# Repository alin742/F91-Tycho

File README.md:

# F91 Tycho

F91 Tycho is a continuation of **[F91 Kepler](https://github.com/drpykachu/F91_Kepler)** by Pegor (originally on [GitLab](https://gitlab.com/_Pegor/kepler_fw)), a full replacement of the Casio F-91W internals with an OLED display and a Bluetooth CC2640R2 MCU. All credit for the original design goes to them; this repo keeps their full history and MIT license.

What's new here:
- **Rechargeable v2:** LIR2016 cell, BQ25180 charger, TPS62840 buck, and a small charging PCB in the case back's dip with a magnetic pogo cable ([main board](Hardware/KiCad/F91-Main_board_v2/README.md), [charging PCB](Hardware/KiCad/F91-Charge_pad/README.md), [JLC panel](Hardware/KiCad/panel/README.md)).
- **KiCad import** of the original DipTrace boards (`Hardware/KiCad/`).
- **Firmware:** battery-life work, v2 charger/battery support (written, not yet compiled).
- **SolidCraft** case + electronics model (`Hardware/SolidCraft/`).
- Open work: [TASKS.md](TASKS.md).

Code identifiers (`f91_kepler.c`, project names, file names) keep the Kepler name so the original build setup still works.

---

## Original F91 Kepler README

## 8/8/25 - This project hasn't been active for a while, but I have kept it around for anyone interested in it or wants to draw inspiration from it. I have moved it from its [original repo](https://gitlab.com/_Pegor/kepler_fw) since I use GitHub more these days. 

The F91 Kepler is complete redesign of the classic Casio F91W watch. This project completely replaces the original internals of the watch only keeping the original case and adding an OLED display and a bluetooth capable MCU.

This repo contains all the firmware, hardware, and completely unfinished software (phone app) ;).

## As of 7/18/22 the current state of the project is:
- Bluetooth capable and supports several calls.
- Only operates through bluetooth diagnostic apps such as nRF Connect.
- Full screen notifications for calls/texts.
- Notifications bar.
- Only one button currently supported to wake screen.
- Battery life of roughly 15 days with waking screen several times a day.

## To-do / improvements:
- Create phone app to handle sending BLE calls automatically.
- Add ability to set time through buttons.
- Add sound capabilities (PCB already contains traces). 
- Improve battery life and efficiency.
- Improve programming jig (make it easier to use without having to completely dismantle).
- Make rechargeable

### At this point (read more like a year ago) I am burnt out from this project and now I figured to open it up and hopefully more people can be involved.

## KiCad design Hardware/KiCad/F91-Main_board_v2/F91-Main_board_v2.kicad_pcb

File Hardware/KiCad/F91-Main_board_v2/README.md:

# F91 Tycho v2 main board (rechargeable)

LIR2016 rechargeable coin cell → **BQ25180** charger → **TPS62840** buck → **2.0 V** for the CC2640R2,
OLED logic and I2C. The board keeps the v1 outline, holder holes, castellated button contacts,
PCB antenna and the v1 RF matching network. Every assembled part is in the JLCPCB library.

Status: **design files generated, not yet built or tested.** See "Check before ordering" below.

## Files
| File | What |
|---|---|
| `F91-Main_board_v2.kicad_sch` | Schematic (net labels, generated) |
| `F91-Main_board_v2.kicad_pcb` | Board: 24.4 × 24.4 mm, 2 layers, 0.8 mm |
| `F91-Main_board_v2.kicad_pro/.kicad_dru` | JLCPCB 2-layer rules (0.1/0.1 mm tracks, vias 0.45/0.25 and 0.6/0.3, both standard price) + castellation / RF / antenna rules |
| `lib/F91_LCSC.*` | Symbols, footprints, 3D models pulled from LCSC with easyeda2kicad (the footprints JLC places to) |
| `lib/F91_custom.pretty` | Antenna, battery pads, castellations, holes, charge-pin holes (from v1 geometry) |
| `scripts/` | The generators (see "Regenerating") |
| `../F91-Charge_pad/` | Obsolete charging PCB (replaced by the two charge pins) |
| `../panel/` | JLC panel (2 × 2 main boards), fab export |

## Circuit summary
- **Cell:** LIR2016 under the original clamp. Clamp = battery +, the cell's flat side = GND pads (as v1).
- **Charger BQ25180** (U2, DSBGA-8, I2C 0x6A): power-up defaults are safe for the LIR2016 with no firmware (4.20 V, 10 mA, BUVLO 3.0 V). /INT → DIO6 (pin 11). TS/MR left open (TS off, no NTC).
- **Buck TPS62840** (U3, DSBGA-6): EN = SYS, VSET = 1.74 kΩ → 2.0 V, 60 nA Iq. L1 2.2 µH.
- **CC2640R2** in internal-LDO mode: the v1 10 µH DC/DC inductor is removed, DCDC_SW is unconnected. Firmware must disable the DC/DC in ccfg (done in `Startup/ccfg_app_ble.c` for `F91_HW_V2`).
- **Battery sense:** 10 MΩ / 1 MΩ divider + 100 nF into DIO23 (ADC). About 0.38 µA.
- **Buttons:** the clamp arm (battery +) touches the castellation, which drives an N-FET gate (PMZB290UNE, 1 MΩ pull-down); the FET pulls DIO15/25/26 low → buttons are **active-low with internal pull-ups** (firmware `F91_HW_V2`).
- **Display connector J1** (Molex 505066, same position as v1). Top row: GND, SCL, **VBAT (new, for the SSD1306 charge pump VDDB)**. Bottom row: **VDD 2.0 V (was battery)**, SDA, NC.
- **Charging input:** two plated Ø1.3 mm holes (Ø1.7 pads) P1 (+, CHG_IN) and P2 (GND) at board (12.80, −3.40) / (11.19, −5.32), watch (9.75, 6.17) / (8.14, 8.09), 2.5 mm apart. Hand-solder a Ø1.2 mm brass pin in each, sticking 1.85 mm out of the bottom (flush with the inner face of the steel back); they meet the pogo cable through two Ø1.8 mm holes in the steel back. D1 (PMEG3002AEL reverse-polarity Schottky), D2 (TPD1E10B06 ESD) and R24 (1 M pull-down) sit next to them.
- **Programming:** cJTAG pads at the v1 jig positions: GND, VDD (sense only), TMS, TCK (the v1 jig fits). The v1 UART and RESET pads were dropped for space; the XDS110 resets the chip over cJTAG. Power the board from the battery pads or from 5 V on the charge pins, never by back-feeding VDD.
- **No external flash:** firmware updates over Bluetooth must use TI **on-chip OAD**. There was no room for an SPI flash: the bottom corners are cut by the board chamfer or taken by the charge pins.

## Display adapter rework (reuse the v1 adapter, no new board)
The v1 adapter ties SSD1306 VDD (logic, max 3.3 V) and VDDB (charge pump, 3.3–4.2 V) to one connector pin. On v2 that pin carries 2.0 V, so the charge pump needs its own supply:
1. Cut the trace between the SSD1306 **VDDB** pin and VDD/VCC on the adapter.
2. Solder a thin enamelled wire from **VDDB** to the adapter connector pin that mates with J1's **top-right** pin (the free pin next to SCL, carrying VBAT on v2).
3. Optional: remove the adapter's duplicate 10 kΩ I2C pull-ups (the main board has 10 kΩ to VDD).

## Status of the generated board
- **DRC: 0 errors, 0 unconnected pads** (`kicad-cli pcb drc --schematic-parity`). 11 warnings: 10 courtyard overlaps (mostly inherited from v1's placement: castellation vs button pad, MH2 vs C8, TP pads near U1) and one 0.087 mm neck where a track enters Q2's pad.
- **Schematic parity:** all nets match. The only differences reported are KiCad's placeholder names for no-connect pins.
- **ERC:** 0 violations.
- Routing was done by `scripts/router2.py` (own grid router; Freerouting was not available here). Look it over in KiCad before ordering, especially around U1 pins 1–10, the charger (U2) and buck (U3) pockets, and the RF chain (copied unchanged from v1).
- Every via is tented. The cell's negative face sits on Pad3/Pad4 + the U1 thermal-via area (all GND).

## Check before ordering
- JLC stock on order day: CC2640R2FRGZR (600 when checked), BQ25180YBGR, TPS62840YBGR.
- In JLC's placement preview, check the rotation of U1 (QFN), U2/U3 (DSBGA), Q1–Q3 (DFN1006) and J1 (Molex).
- Case-open measurements (TASKS.md): clamp outline, piezo position, case-back thickness, clamp-to-case-back contact. Check the mode-button clamp arm stays clear of the charge pins.

## Regenerating
```
cd Hardware/KiCad/F91-Main_board_v2
python3 scripts/gen_footprints.py     # custom footprints from the v1 board
python3 scripts/gen_project.py        # .kicad_pro rules + .kicad_dru
python3 scripts/gen_sch.py            # schematic from scripts/design.py
python3 scripts/gen_pcb.py            # board: v1 geometry + placement (placement/place.json) + fixed escapes
python3 scripts/fanout_gnd.py         # short track + via for every small GND pad
python3 scripts/router2.py 40         # negotiated-congestion router (all nets but GND)
python3 scripts/nudge_vias.py F91-Main_board_v2.kicad_pcb work/drc.rpt   # after a DRC, fixes ~0.01 mm misses
python3 scripts/pour.py               # GND pours + stitching vias
python3 scripts/link_gnd_clusters.py  # joins any GND piece the pour left isolated
python3 scripts/finalize.py F91-Main_board_v2.kicad_pcb   # hide refdes, board label
../../../tools/kikit-venv/bin/python ../panel/panelize.py
python3 ../panel/export_fab.py        # gerbers zip + JLC BOM/CPL
```
`scripts/design.py` is the single source of truth for parts, values, LCSC numbers and nets.

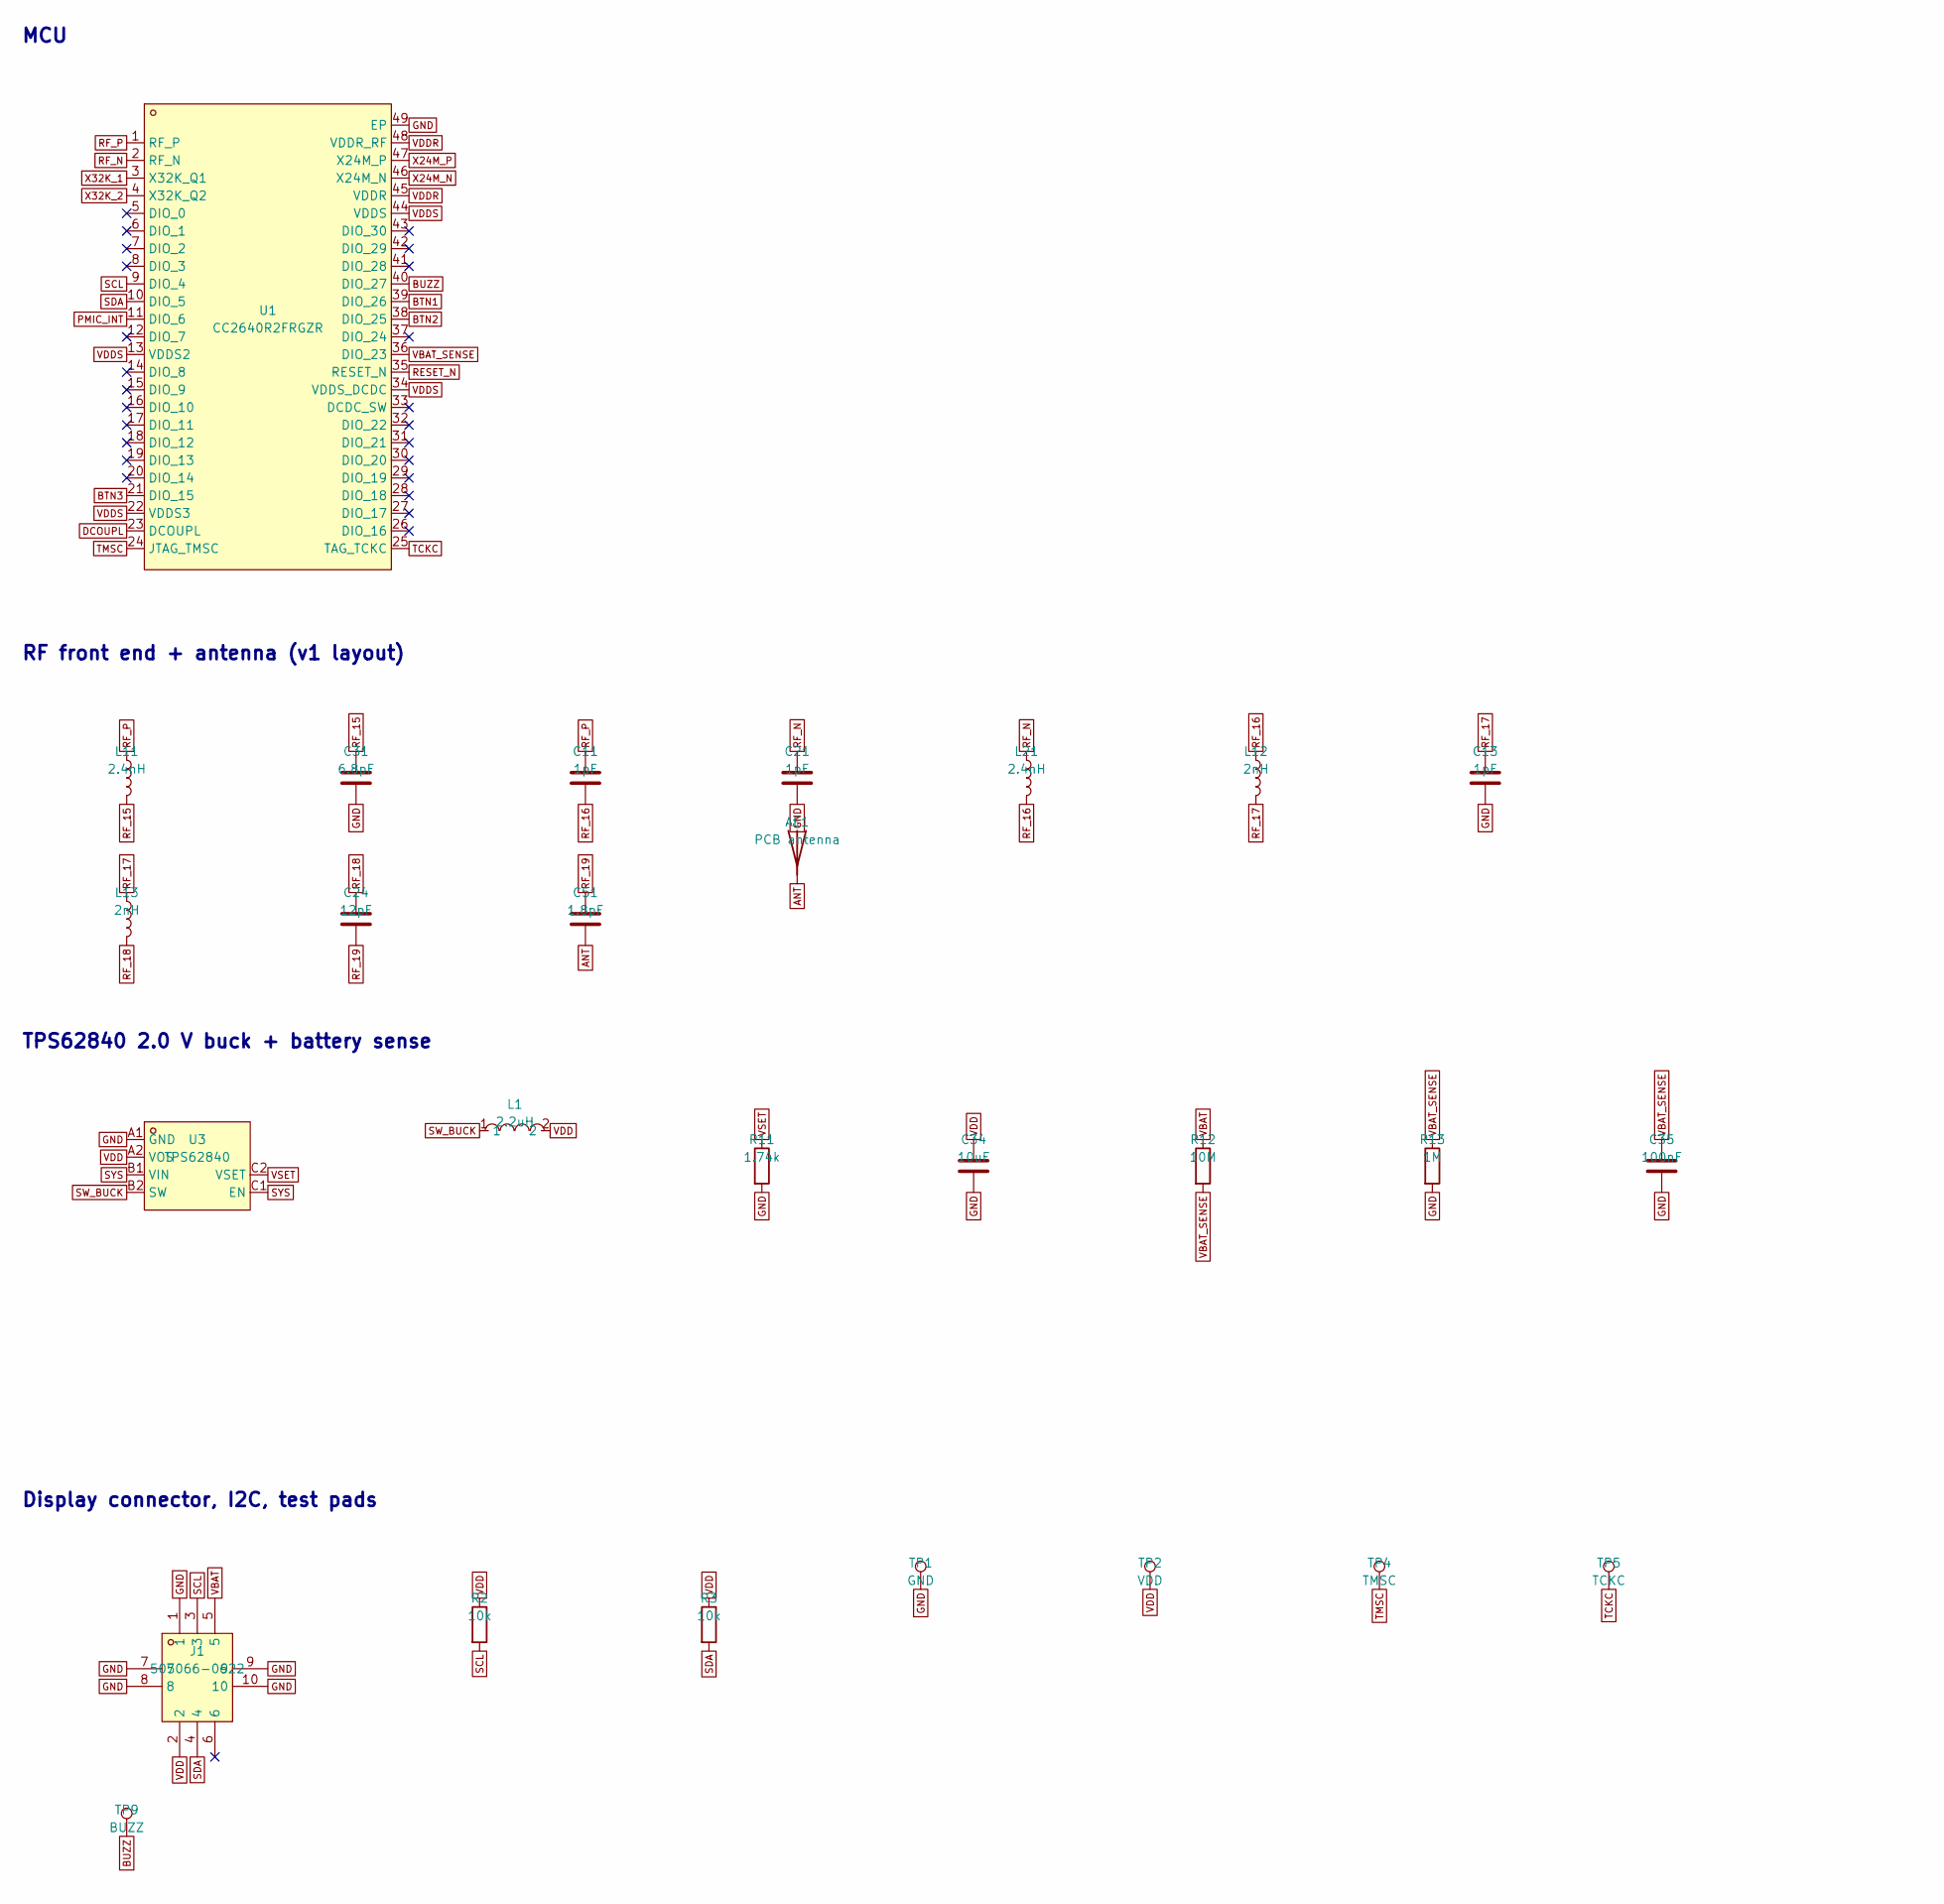
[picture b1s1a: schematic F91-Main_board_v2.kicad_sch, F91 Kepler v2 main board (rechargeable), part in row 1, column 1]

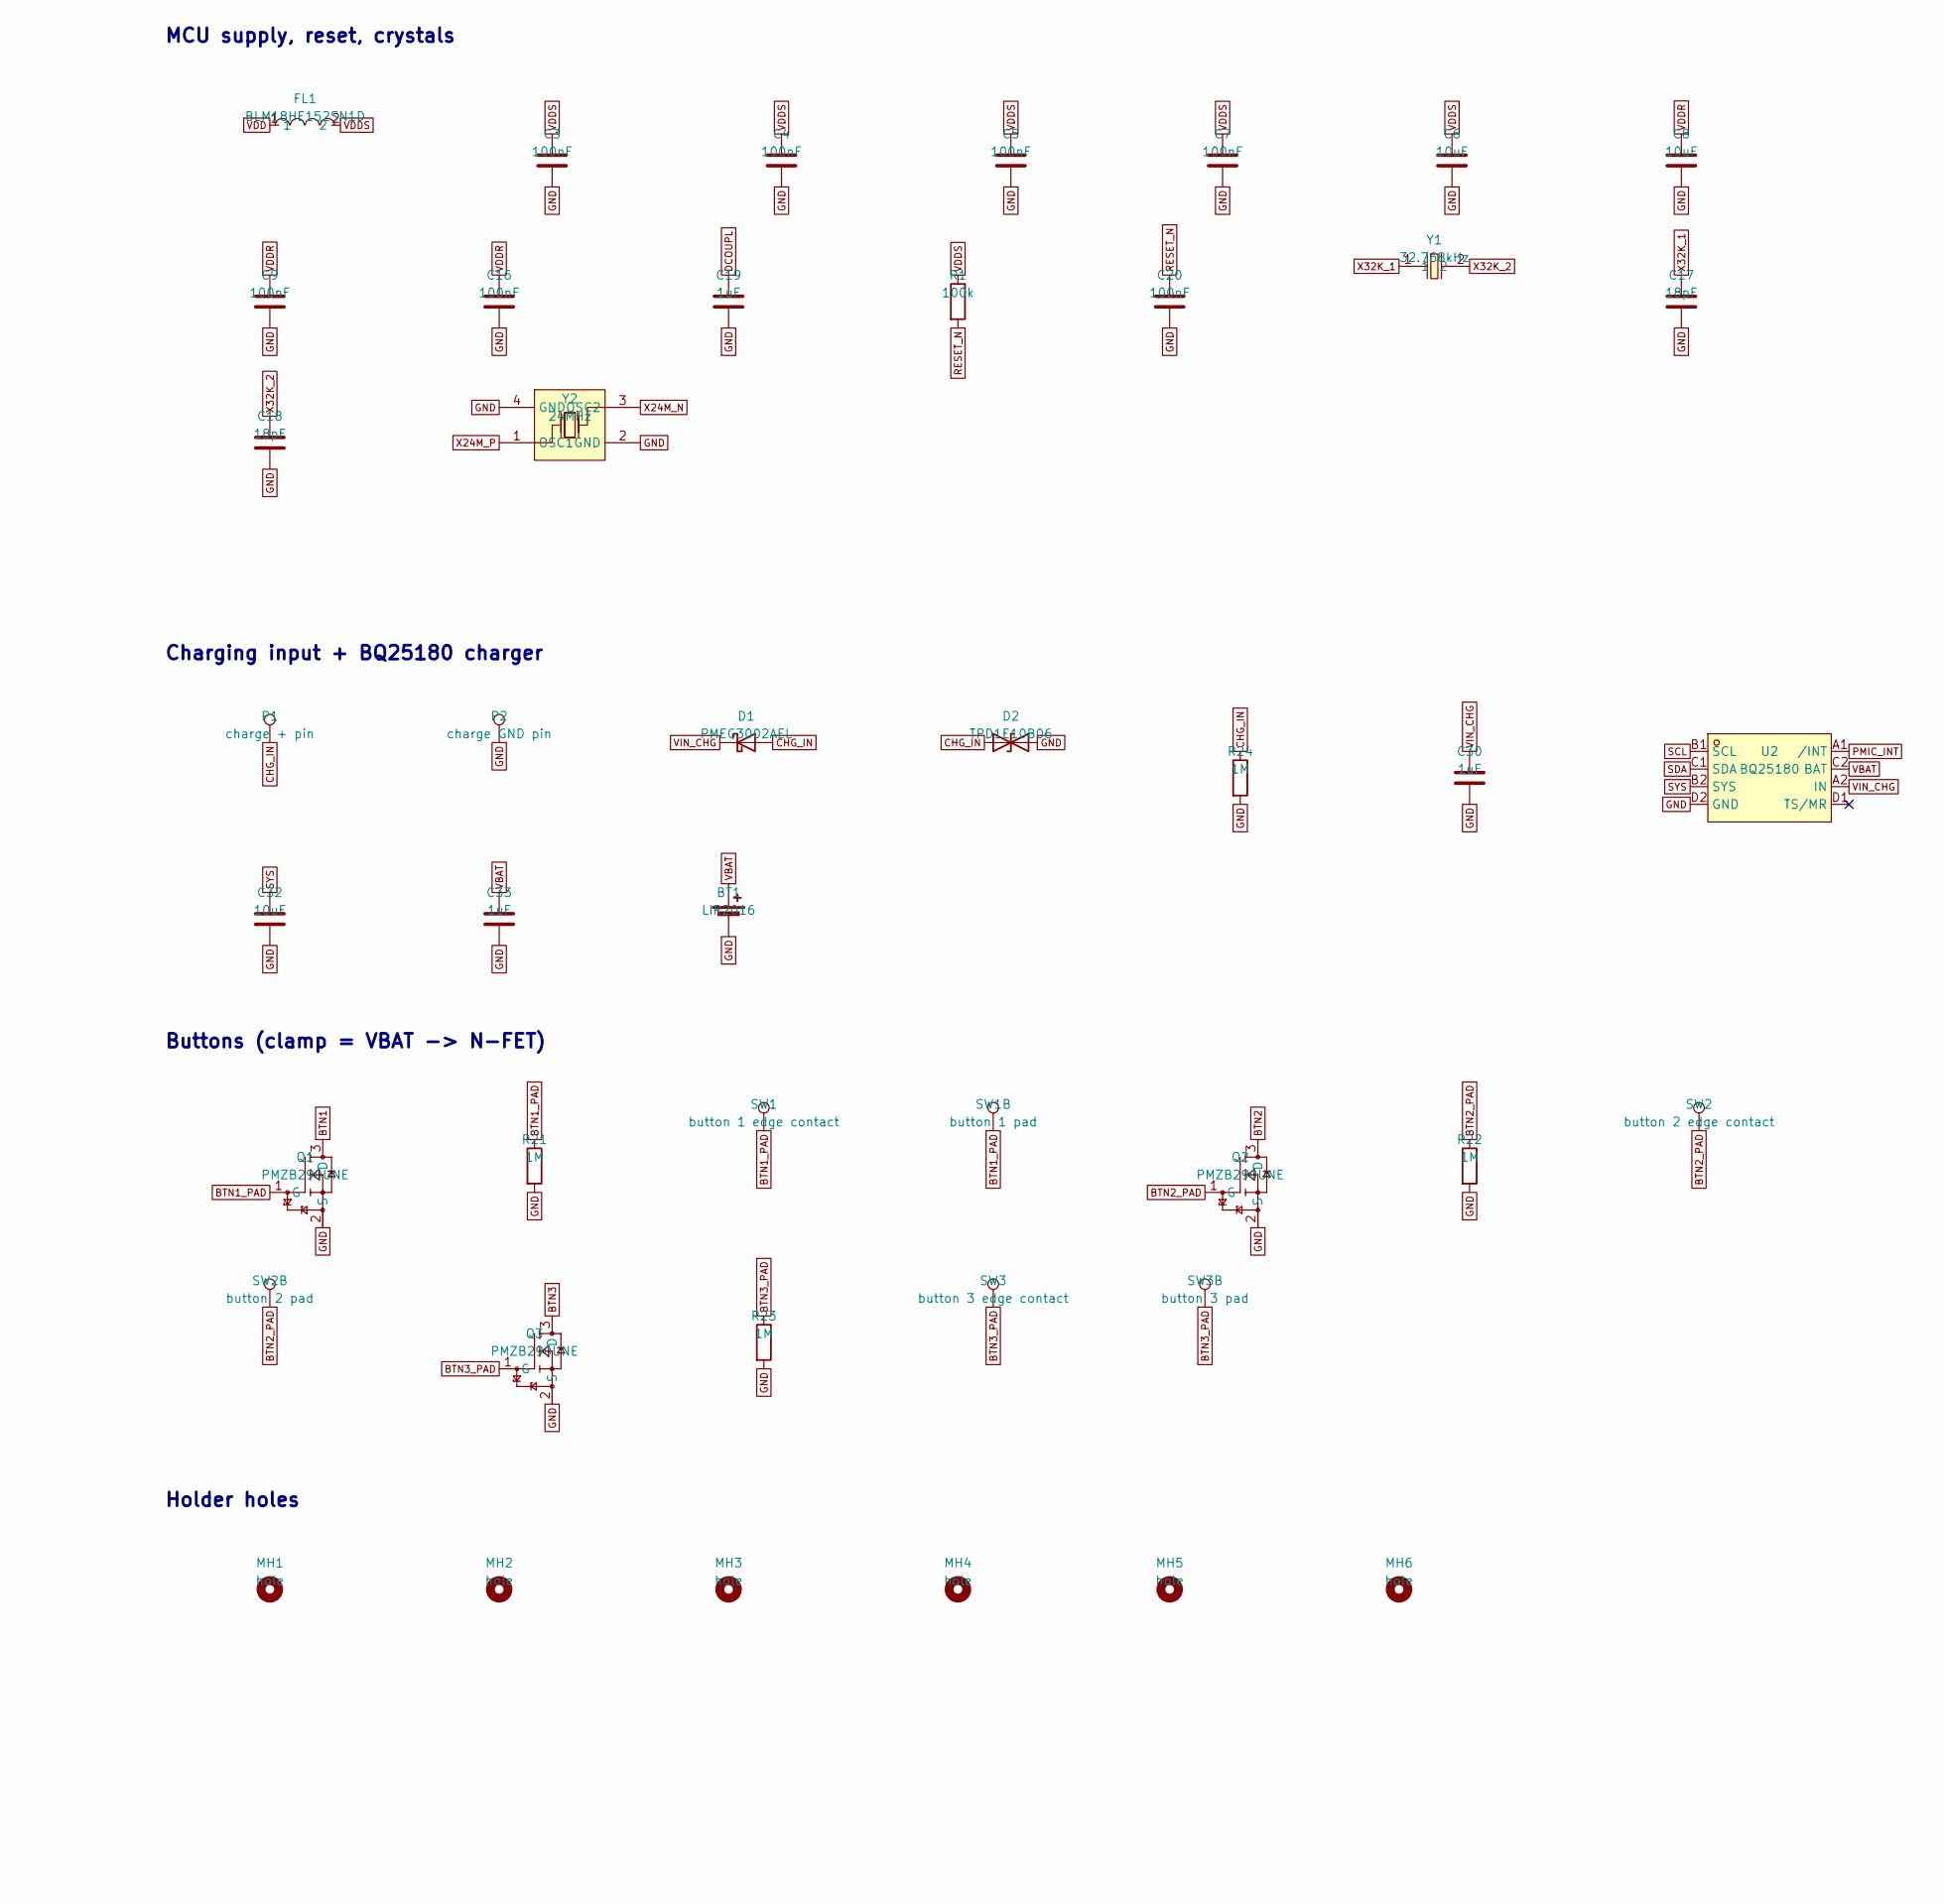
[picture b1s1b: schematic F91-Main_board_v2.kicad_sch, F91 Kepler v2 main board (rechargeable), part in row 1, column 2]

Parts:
AE1: PCB antenna; ANT_TI_MEANDER_B
BT1: LIR2016; BAT_LIR2016_CLAMP
C3, C4, C5, C7, C9, C16, C20, C35: 100nF; C_0402_1005Metric; LCSC C1525
C6, C8: 10uF; C_0603_1608Metric; LCSC C19702
C11, C13, C21: 1pF; C_0402_1005Metric; LCSC C1550
C17, C18: 18pF; C_0402_1005Metric; LCSC C1549
C19, C30, C33: 1uF; C_0402_1005Metric; LCSC C52923
C24: 12pF; C_0402_1005Metric; LCSC C1547
C31: 6.8pF; C_0402_1005Metric; LCSC C1576
C32, C34: 10uF; C_0402_1005Metric; LCSC C15525
C51: 1.8pF; C_0402_1005Metric; LCSC C1553
D1: PMEG3002AEL; SOD-882_L1.0-W0.6-RD; LCSC C478015
D2: TPD1E10B06; X1SON-2_L1.0-W0.6-P0.65-BI-1; LCSC C48260
FL1: BLM18HE152SN1D; L0603; LCSC C82155
J1: 505066-0622; CONN-SMD_5050660622; LCSC C724122
L1: 2.2uH; L0603; LCSC C98342
L11, L21: 2.4nH; L_0402_1005Metric; LCSC C97997
L12, L13: 2nH; L_0402_1005Metric; LCSC C18216
MH1, MH2: hole; NPTH_D0.8
MH3, MH4, MH5, MH6: hole; NPTH_D1.1
P1: charge + pin; PIN_PTH_D1.25
P2: charge GND pin; PIN_PTH_D1.25
Q1, Q2, Q3: PMZB290UNE; X1-DFN1006-3_L1.0-W0.6-BR; LCSC C222570
R1: 100k; R_0402_1005Metric; LCSC C25741
R2, R3: 10k; R_0402_1005Metric; LCSC C25744
R11: 1.74k; R_0402_1005Metric; LCSC C226859
R12: 10M; R_0402_1005Metric; LCSC C26082
R13, R21, R22, R23, R24: 1M; R_0402_1005Metric; LCSC C26083
SW1: button 1 edge contact; BTN_CASTELLATION_D4
SW1B: button 1 pad; BTN_PAD_0.7x0.6
SW2: button 2 edge contact; BTN_CASTELLATION_D4
SW2B: button 2 pad; BTN_PAD_0.7x0.6
SW3: button 3 edge contact; BTN_CASTELLATION_D4
SW3B: button 3 pad; BTN_PAD_0.7x0.6
TP1: GND; TP_ROUND_D0.7
TP2: VDD; TP_ROUND_D0.7
TP4: TMSC; TP_ROUND_D0.7
TP5: TCKC; TP_ROUND_D0.7
TP9: BUZZ; PAD_ROUND_D1.5_B
U1: CC2640R2FRGZR; Texas_RGZ0048A_VQFN-48-1EP_7x7mm_P0.5mm_EP5.15x5.15mm_Therm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; LCSC C122885
U2: BQ25180; DSBGA-8_L1.6-W0.9-R2-C4-P0.40-BL; LCSC C3682423
U3: TPS62840; DSBGA-6_L1.4-W1.0-R2-C3-P0.40-BL; LCSC C2071139
Y1: 32.768kHz; FC-135R_L3.2-W1.5; LCSC C32346
Y2: 24MHz; CRYSTAL-SMD_4P-L3.2-W2.5-BL; LCSC C89577

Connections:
ANT: AE1.1, C51.2
BTN1: Q1.3 (D), U1.39 (DIO_26)
BTN1_PAD: Q1.1 (G), R21.1, SW1.1, SW1B.1
BTN2: Q2.3 (D), U1.38 (DIO_25)
BTN2_PAD: Q2.1 (G), R22.1, SW2.1, SW2B.1
BTN3: Q3.3 (D), U1.21 (DIO_15)
BTN3_PAD: Q3.1 (G), R23.1, SW3.1, SW3B.1
BUZZ: TP9.1, U1.40 (DIO_27)
CHG_IN: D1.2 (A), D2.1 (A1), P1.1, R24.1
DCOUPL: C19.1, U1.23 (DCOUPL)
GND: BT1.2 (-), C3.2, C4.2, C5.2, C6.2, C7.2, C8.2, C9.2, C13.2, C16.2, C17.2, C18.2, C19.2, C20.2, C21.2, C30.2, C31.2, C32.2, C33.2, C34.2, C35.2, D2.2 (A2), J1.1, J1.7, J1.8, J1.9, J1.10, P2.1, Q1.2 (S), Q2.2 (S), Q3.2 (S), R11.2, R13.2, R21.2, R22.2, R23.2, R24.2, TP1.1, U1.49 (EP), U2.D2 (GND), U3.A1 (GND), Y2.2 (GND), Y2.4 (GND)
PMIC_INT: U1.11 (DIO_6), U2.A1 (/INT)
RESET_N: C20.1, R1.2, U1.35 (RESET_N)
RF_15: C31.1, L11.2
RF_16: C11.2, L12.1, L21.2
RF_17: C13.1, L12.2, L13.1
RF_18: C24.1, L13.2
RF_19: C24.2, C51.1
RF_N: C21.1, L21.1, U1.2 (RF_N)
RF_P: C11.1, L11.1, U1.1 (RF_P)
SCL: J1.3, R2.2, U1.9 (DIO_4), U2.B1 (SCL)
SDA: J1.4, R3.2, U1.10 (DIO_5), U2.C1 (SDA)
SW_BUCK: L1.1, U3.B2 (SW)
SYS: C32.1, U2.B2 (SYS), U3.B1 (VIN), U3.C1 (EN)
TCKC: TP5.1, U1.25 (TAG_TCKC)
TMSC: TP4.1, U1.24 (JTAG_TMSC)
VBAT: BT1.1 (+), C33.1, J1.5, R12.1, U2.C2 (BAT)
VBAT_SENSE: C35.1, R12.2, R13.1, U1.36 (DIO_23)
VDD: C34.1, FL1.1, J1.2, L1.2, R2.1, R3.1, TP2.1, U3.A2 (VOS)
VDDR: C8.1, C9.1, C16.1, U1.45 (VDDR), U1.48 (VDDR_RF)
VDDS: C3.1, C4.1, C5.1, C6.1, C7.1, FL1.2, R1.1, U1.13 (VDDS2), U1.22 (VDDS3), U1.34 (VDDS_DCDC), U1.44 (VDDS)
VIN_CHG: C30.1, D1.1 (K), U2.A2 (IN)
VSET: R11.1, U3.C2 (VSET)
X24M_N: U1.46 (X24M_N), Y2.3 (OSC2)
X24M_P: U1.47 (X24M_P), Y2.1 (OSC1)
X32K_1: C17.1, U1.3 (X32K_Q1), Y1.1
X32K_2: C18.1, U1.4 (X32K_Q2), Y1.2

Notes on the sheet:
MCU
MCU supply, reset, crystals
RF front end + antenna (v1 layout)
Charging input + BQ25180 charger
TPS62840 2.0 V buck + battery sense
Buttons (clamp = VBAT -> N-FET)
Display connector, I2C, test pads
Holder holes

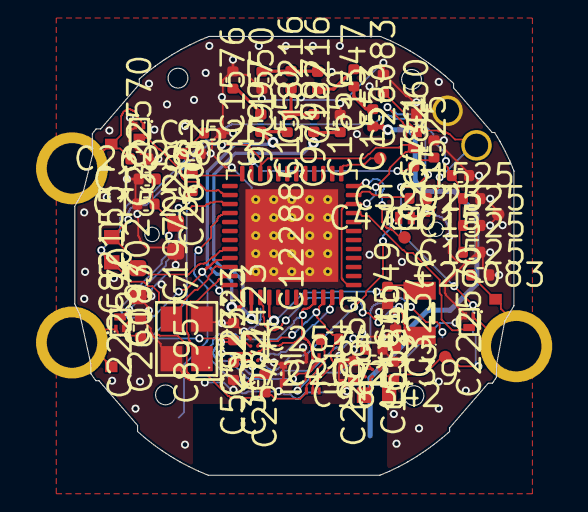
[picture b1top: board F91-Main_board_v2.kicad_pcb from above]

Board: 2 copper layers, 24.4 x 24.4 mm, 71 parts (0 on the bottom side), 37 nets.

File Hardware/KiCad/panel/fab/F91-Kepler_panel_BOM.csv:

Comment,Designator,Footprint,LCSC Part #
CC2640R2FRGZR,"U1_M1,U1_M2,U1_M3,U1_M4",Texas_RGZ0048A_VQFN-48-1EP_7x7mm_P0.5mm_EP5.15x5.15mm_ThermalVias,C122885
100nF,"C16_M1,C16_M2,C16_M3,C16_M4,C20_M1,C20_M2,C20_M3,C20_M4,C35_M1,C35_M2,C35_M3,C35_M4,C3_M1,C3_M2,C3_M3,C3_M4,C4_M1,C4_M2,C4_M3,C4_M4,C5_M1,C5_M2,C5_M3,C5_M4,C7_M1,C7_M2,C7_M3,C7_M4,C9_M1,C9_M2,C9_M3,C9_M4",C_0402_1005Metric,C1525
12pF,"C24_M1,C24_M2,C24_M3,C24_M4",C_0402_1005Metric,C1547
18pF,"C17_M1,C17_M2,C17_M3,C17_M4,C18_M1,C18_M2,C18_M3,C18_M4",C_0402_1005Metric,C1549
1pF,"C11_M1,C11_M2,C11_M3,C11_M4,C13_M1,C13_M2,C13_M3,C13_M4,C21_M1,C21_M2,C21_M3,C21_M4",C_0402_1005Metric,C1550
10uF,"C32_M1,C32_M2,C32_M3,C32_M4,C34_M1,C34_M2,C34_M3,C34_M4",C_0402_1005Metric,C15525
1.8pF,"C51_M1,C51_M2,C51_M3,C51_M4",C_0402_1005Metric,C1553
6.8pF,"C31_M1,C31_M2,C31_M3,C31_M4",C_0402_1005Metric,C1576
2nH,"L12_M1,L12_M2,L12_M3,L12_M4,L13_M1,L13_M2,L13_M3,L13_M4",L_0402_1005Metric,C18216
10uF,"C6_M1,C6_M2,C6_M3,C6_M4,C8_M1,C8_M2,C8_M3,C8_M4",C_0603_1608Metric,C19702
TPS62840,"U3_M1,U3_M2,U3_M3,U3_M4",DSBGA-6_L1.4-W1.0-R2-C3-P0.40-BL,C2071139
PMZB290UNE,"Q1_M1,Q1_M2,Q1_M3,Q1_M4,Q2_M1,Q2_M2,Q2_M3,Q2_M4,Q3_M1,Q3_M2,Q3_M3,Q3_M4",X1-DFN1006-3_L1.0-W0.6-BR,C222570
1.74k,"R11_M1,R11_M2,R11_M3,R11_M4",R_0402_1005Metric,C226859
100k,"R1_M1,R1_M2,R1_M3,R1_M4",R_0402_1005Metric,C25741
10k,"R2_M1,R2_M2,R2_M3,R2_M4,R3_M1,R3_M2,R3_M3,R3_M4",R_0402_1005Metric,C25744
10M,"R12_M1,R12_M2,R12_M3,R12_M4",R_0402_1005Metric,C26082
1M,"R13_M1,R13_M2,R13_M3,R13_M4,R21_M1,R21_M2,R21_M3,R21_M4,R22_M1,R22_M2,R22_M3,R22_M4,R23_M1,R23_M2,R23_M3,R23_M4,R24_M1,R24_M2,R24_M3,R24_M4",R_0402_1005Metric,C26083
32.768kHz,"Y1_M1,Y1_M2,Y1_M3,Y1_M4",FC-135R_L3.2-W1.5,C32346
BQ25180,"U2_M1,U2_M2,U2_M3,U2_M4",DSBGA-8_L1.6-W0.9-R2-C4-P0.40-BL,C3682423
PMEG3002AEL,"D1_M1,D1_M2,D1_M3,D1_M4",SOD-882_L1.0-W0.6-RD,C478015
TPD1E10B06,"D2_M1,D2_M2,D2_M3,D2_M4",X1SON-2_L1.0-W0.6-P0.65-BI-1,C48260
1uF,"C19_M1,C19_M2,C19_M3,C19_M4,C30_M1,C30_M2,C30_M3,C30_M4,C33_M1,C33_M2,C33_M3,C33_M4",C_0402_1005Metric,C52923
505066-0622,"J1_M1,J1_M2,J1_M3,J1_M4",CONN-SMD_5050660622,C724122
BLM18HE152SN1D,"FL1_M1,FL1_M2,FL1_M3,FL1_M4",L0603,C82155
24MHz,"Y2_M1,Y2_M2,Y2_M3,Y2_M4",CRYSTAL-SMD_4P-L3.2-W2.5-BL,C89577
2.4nH,"L11_M1,L11_M2,L11_M3,L11_M4,L21_M1,L21_M2,L21_M3,L21_M4",L_0402_1005Metric,C97997
2.2uH,"L1_M1,L1_M2,L1_M3,L1_M4",L0603,C98342

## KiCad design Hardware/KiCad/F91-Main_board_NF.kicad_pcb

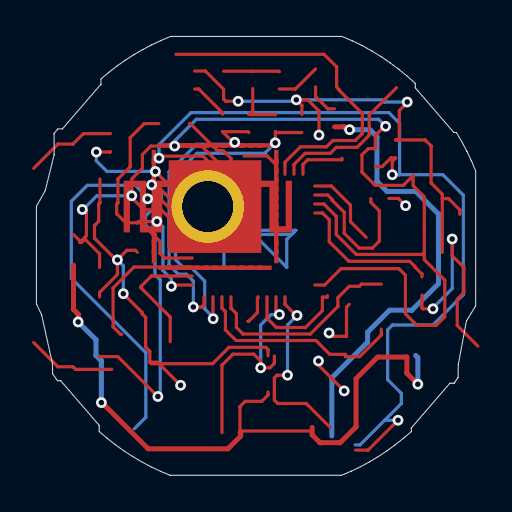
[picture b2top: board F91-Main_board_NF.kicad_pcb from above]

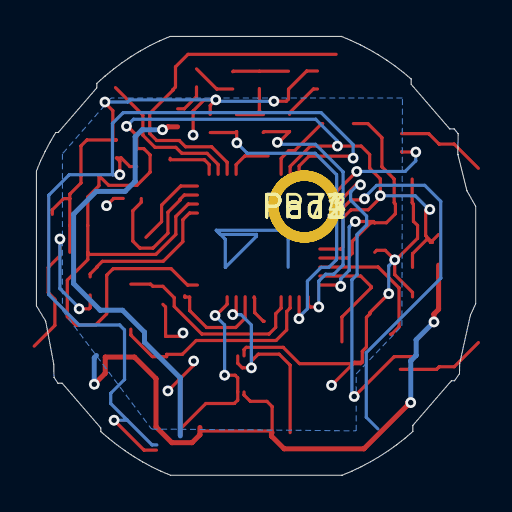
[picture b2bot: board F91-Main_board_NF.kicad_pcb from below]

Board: 2 copper layers, 24.4 x 24.4 mm, 64 parts (7 on the bottom side), 20 nets.

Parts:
C3, C4, C5, C7, C9, C16, C20: 100nF; CAP_0402
C6, C8: 10uF; CAP_0603
C11, C13, C21: 1pF; CAP_0402
C17, C18, C24: 12pF; CAP_0402
C19: 1uF; CAP_0402
C31: 6.8pF; CAP_0402
C51: 1.8pF; CAP_0402
FL1: CAP_0603
GND: single_probe_point
L1: 10uH; IND_0805
L11, L21: 2.4nH; IND_0402
L12, L13: 2nH; IND_0402
MH1, MH2, MH3, MH4, MH5, MH6: 1pin
P5, P6, P7: CONN_01X01
Pad1, Pad2, Pad3, Pad4, Pad5, Pad6, Pad7: (no value)
R1: 100k; RES_0402
R2, R3: 3.3k; RES_0402
R4, R5, R6: 100; RES_0402
RESET: N/A DO NOT CONNECT; RES_0402
SW0: single_probe_point
Switch1, Switch2, Switch3: SingleConnect
TDI: single_probe_point
TDO: single_probe_point
U2: BT_ANTENNA
U3: 5050660622
WMCU_RESET: single_probe_point
WMCU_RXD: single_probe_point
WMCU_TCK: single_probe_point
WMCU_TMS: single_probe_point
WMCU_TXD: single_probe_point
WMCU_VDD: single_probe_point
Y1: 32.768kHz; FC-135
Y2: 24MHz; TSX-3225

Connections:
Net 0: C3.1, C4.1, C5.1, C6.1, C7.1, C8.1, C9.1, C13.1, C16.1, C17.1, C18.1, C19.1, C20.1, C21.1, C31.2, GND.1, Pad3.1, Pad4.1, Pad6.1, Pad7.1, RESET.1, U3.1, Y2.2, Y2.4
Net 1: FL1.1, Pad1.1, Pad2.1, R2.1, R3.1, U3.4, WMCU_VDD.1
Net 2: C3.2, C4.2, C5.2, C6.2, C7.2, FL1.2, R1.2
Net 4: C8.2, C9.2, C16.2, L1.2
Net 7: C20.2, R1.1, RESET.2, WMCU_RESET.1
Net 8: C17.2, Y1.1
Net 9: C18.2, Y1.2
Net 13: C21.2, L21.2
Net 14: C11.2, L11.1
Net 15: C31.1, L11.2
Net 16: C11.1, L12.2, L21.1
Net 17: C13.2, L12.1, L13.2
Net 18: C24.2, L13.1
Net 19: C24.1, C51.2
Net 20: C51.1, U2.1
Net 30: R3.2, U3.5
Net 31: R2.2, U3.2
Net 35: P6.1, R4.1, Switch1.1
Net 36: P5.1, R5.1, Switch2.1
Net 37: P7.1, R6.1, Switch3.1

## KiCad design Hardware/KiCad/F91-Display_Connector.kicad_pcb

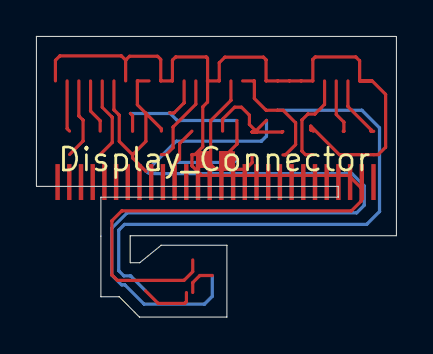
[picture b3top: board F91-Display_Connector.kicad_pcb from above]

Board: 2 copper layers, 20.0 x 15.6 mm, 7 parts (0 on the bottom side), 10 nets.

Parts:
C1, C2: 1uF; CAP_0402
C3: 10uF; CAP_0402
C4, C5: 4.7uF; CAP_0402
D1: DIO_0402
Display_Connector: 0.83-OLED_28pin

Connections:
Net 0: C3.1, C4.1, C5.1, Display_Connector.1, Display_Connector.7, Display_Connector.10, Display_Connector.11, Display_Connector.14, Display_Connector.15, Display_Connector.19, Display_Connector.20, Display_Connector.21, Display_Connector.22, Display_Connector.23, Display_Connector.27, Display_Connector.28
Net 1: C1.1, Display_Connector.2
Net 2: C1.2, Display_Connector.3
Net 3: C2.1, Display_Connector.4
Net 4: C2.2, Display_Connector.5
Net 5: D1.1, Display_Connector.6, Display_Connector.8, Display_Connector.9
Net 6: C3.2, D1.2, Display_Connector.12
Net 8: Display_Connector.17, Display_Connector.18
Net 10: C4.2, Display_Connector.25
Net 11: C5.2, Display_Connector.26
